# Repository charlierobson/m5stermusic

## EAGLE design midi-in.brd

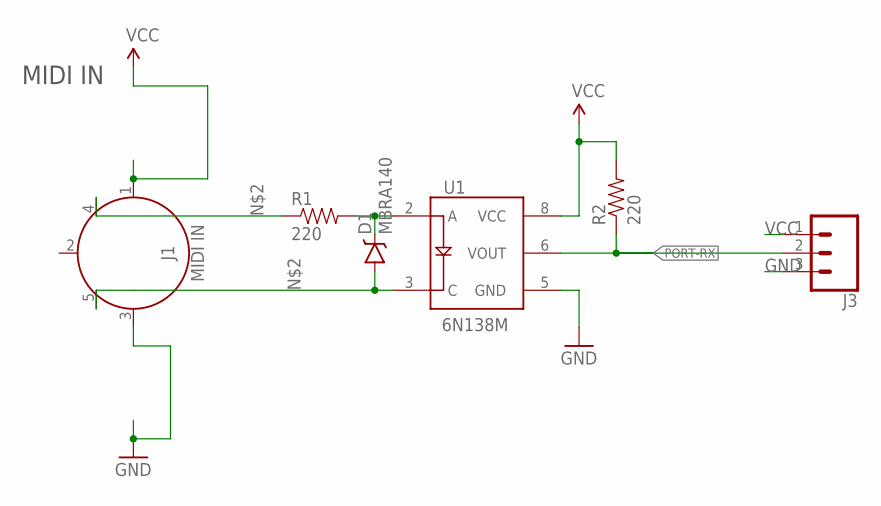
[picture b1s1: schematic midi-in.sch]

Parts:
D1: MBRA140; SMA-DIODE
J1: MIDI IN; 5-PIN-DIN-RA-PCB-NEW
J3: CONN_03; 1X03
R1, R2: 220; 0603-RES
U1: 6N138M; 8-SMD

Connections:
56: D1.C, R1.2, U1.2 (A)
GND: J1.3, J3.3, U1.5 (GND)
unnamed: J1.4, R1.1
PIN5: D1.A, J1.5, U1.3 (C)
PORT-RX: J3.2, R2.1, U1.6 (VOUT)
VCC: J1.1, J3.1, R2.2, U1.8 (VCC)

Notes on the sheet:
MIDI IN

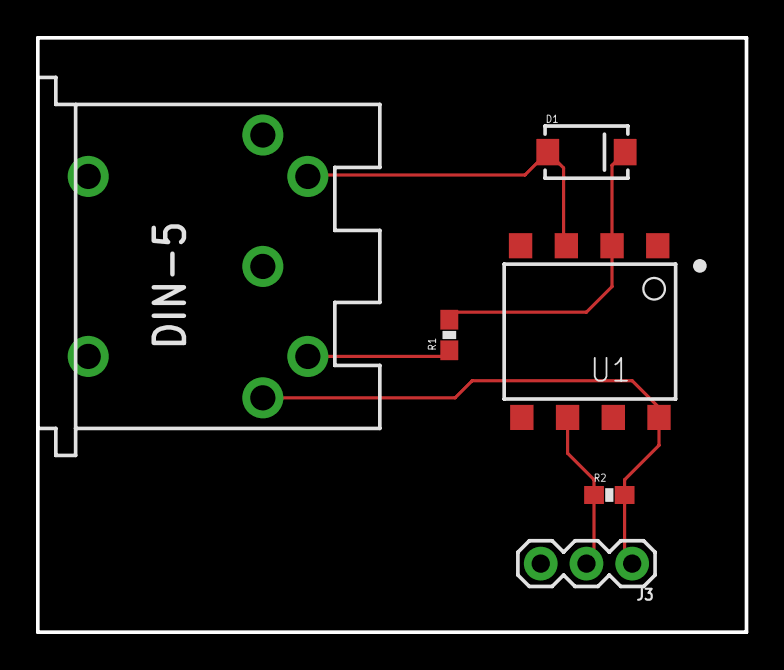
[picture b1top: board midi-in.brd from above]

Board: 3 copper layers, 39.4 x 33.0 mm, 6 parts (0 on the bottom side), 6 nets.

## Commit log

2019-11-11 add midi in board

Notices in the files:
parts and their libraries:
SparkFun-Resistors: Licensing: Creative Commons ShareAlike 4.0 International - https://creativecommons.org/licenses/by-sa/4.0
